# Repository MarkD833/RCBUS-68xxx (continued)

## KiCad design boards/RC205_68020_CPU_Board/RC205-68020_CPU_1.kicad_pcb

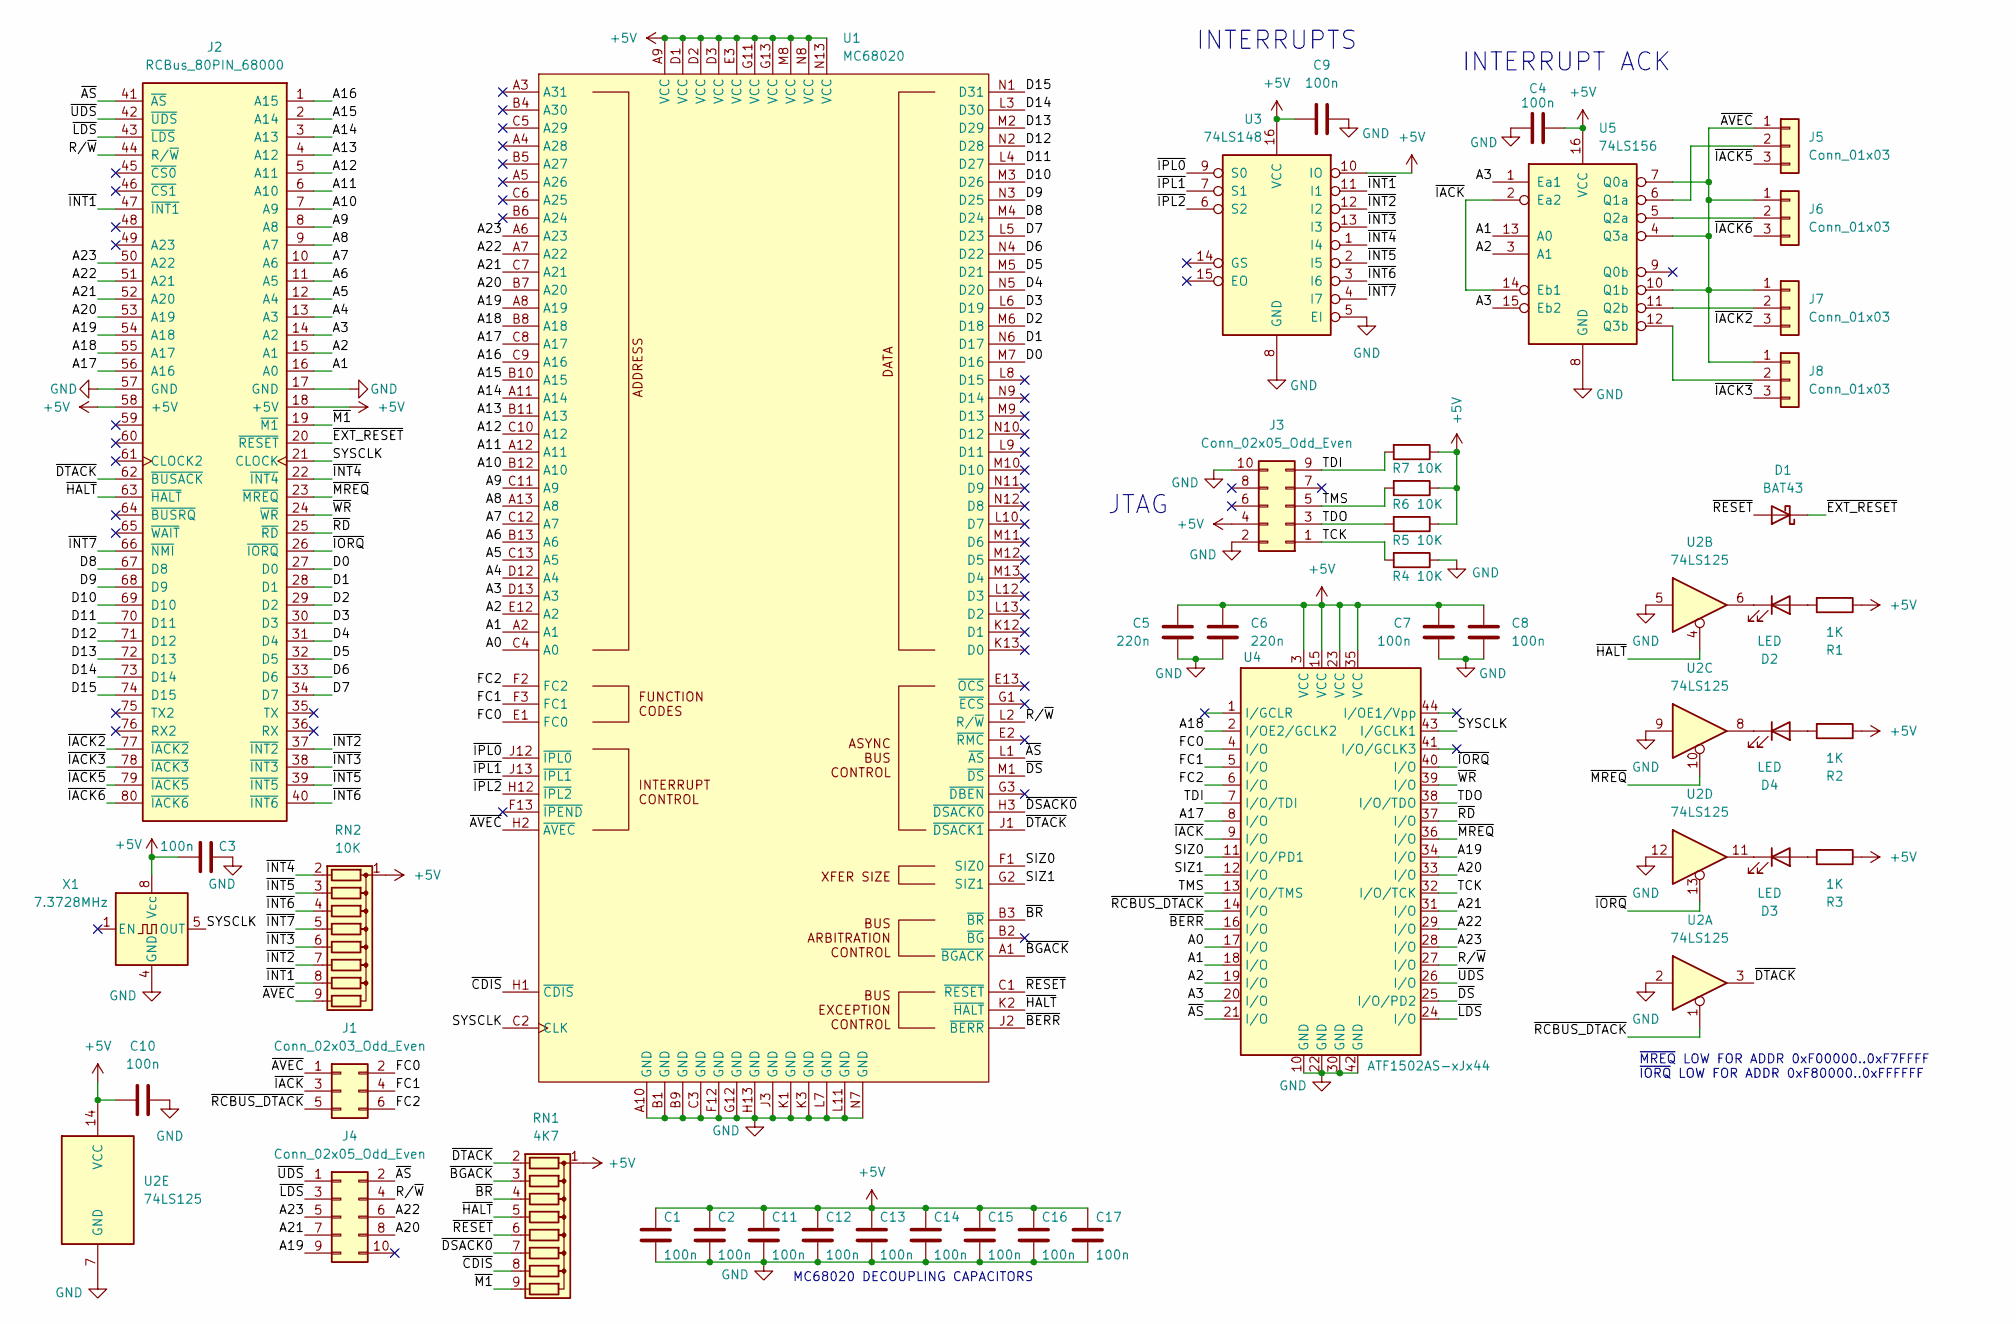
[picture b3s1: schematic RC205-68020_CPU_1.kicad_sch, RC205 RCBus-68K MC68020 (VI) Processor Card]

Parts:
C1, C2, C3, C4, C7, C8, C9, C10, C11, C12, C13, C14, C15, C16, C17: 100n; C_0805_2012Metric_Pad1.18x1.45mm_HandSolder
C5, C6: 220n; C_0805_2012Metric_Pad1.18x1.45mm_HandSolder
D1: BAT43; D_DO-35_SOD27_P7.62mm_Horizontal
D2, D3, D4: LED; LED_D3.0mm
J1: Conn_02x03_Odd_Even; PinHeader_2x03_P2.54mm_Vertical
J2: RCBus_80PIN_68000; RCBus_80p_Medium
J3, J4: Conn_02x05_Odd_Even; PinHeader_2x05_P2.54mm_Vertical
J5, J6, J7, J8: Conn_01x03; PinHeader_1x03_P2.54mm_Vertical
R1, R2, R3: 1K; R_0805_2012Metric_Pad1.20x1.40mm_HandSolder
R4, R5, R6, R7: 10K; R_0805_2012Metric_Pad1.20x1.40mm_HandSolder
RN1: 4K7; R_Array_SIP9
RN2: 10K; R_Array_SIP9
U1: MC68020; PGA114
U2: 74LS125; DIP-14_W7.62mm
U3: 74LS148; DIP-16_W7.62mm
U4: ATF1502AS-xJx44; PLCC-44_THT-Socket
U5: 74LS156; DIP-16_W7.62mm
X1: 7.3728MHz; Oscillator_DIP-8

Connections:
+5V: C1.2, C2.2, C3.2, C4.1, C5.2, C6.2, C7.1, C8.2, C9.1, C10.1, C11.2, C12.2, C13.2, C14.2, C15.2, C16.2, C17.2, J2.18 (+5V), J2.58 (+5V), J3.4, R1.1, R2.1, R3.1, R5.1, R6.1, R7.1, RN1.1 (common), RN2.1 (common), U1.A9 (VCC), U1.D1 (VCC), U1.D2 (VCC), U1.D3 (VCC), U1.E3 (VCC), U1.G11 (VCC), U1.G13 (VCC), U1.M8 (VCC), U1.N8 (VCC), U1.N13 (VCC), U2.14 (VCC), U3.10 (IO), U3.16 (VCC), U4.3 (VCC), U4.15 (VCC), U4.23 (VCC), U4.35 (VCC), U5.16 (VCC), X1.8 (Vcc)
/A0: U1.C4 (A0), U4.17 (I/O)
/A1: J2.16 (A0), U1.A2 (A1), U4.18 (I/O), U5.13 (A0)
/A2: J2.15 (A1), U1.E12 (A2), U4.19 (I/O), U5.3 (A1)
/A3: J2.14 (A2), U1.D13 (A3), U4.20 (I/O), U5.1 (Ea1), U5.15 (Eb2)
/A4: J2.13 (A3), U1.D12 (A4)
/A5: J2.12 (A4), U1.C13 (A5)
/A6: J2.11 (A5), U1.B13 (A6)
/A7: J2.10 (A6), U1.C12 (A7)
/A8: J2.9 (A7), U1.A13 (A8)
/A9: J2.8 (A8), U1.C11 (A9)
/A10: J2.7 (A9), U1.B12 (A10)
/A11: J2.6 (A10), U1.A12 (A11)
/A12: J2.5 (A11), U1.C10 (A12)
/A13: J2.4 (A12), U1.B11 (A13)
/A14: J2.3 (A13), U1.A11 (A14)
/A15: J2.2 (A14), U1.B10 (A15)
/A16: J2.1 (A15), U1.C9 (A16)
/A17: J2.56 (A16), U1.C8 (A17), U4.8 (I/O)
/A18: J2.55 (A17), U1.B8 (A18), U4.2 (I/OE2/GCLK2)
/A19: J2.54 (A18), J4.9, U1.A8 (A19), U4.34 (I/O)
/A20: J2.53 (A19), J4.8, U1.B7 (A20), U4.33 (I/O)
/A21: J2.52 (A20), J4.7, U1.C7 (A21), U4.31 (I/O)
/A22: J2.51 (A21), J4.6, U1.A7 (A22), U4.29 (I/O)
/A23: J2.50 (A22), J4.5, U1.A6 (A23), U4.28 (I/O)
/D0: J2.27 (D0), U1.M7 (D16)
/D1: J2.28 (D1), U1.N6 (D17)
/D2: J2.29 (D2), U1.M6 (D18)
/D3: J2.30 (D3), U1.L6 (D19)
/D4: J2.31 (D4), U1.N5 (D20)
/D5: J2.32 (D5), U1.M5 (D21)
/D6: J2.33 (D6), U1.N4 (D22)
/D7: J2.34 (D7), U1.L5 (D23)
/D8: J2.67 (D8), U1.M4 (D24)
/D9: J2.68 (D9), U1.N3 (D25)
/D10: J2.69 (D10), U1.M3 (D26)
/D11: J2.70 (D11), U1.L4 (D27)
/D12: J2.71 (D12), U1.N2 (D28)
/D13: J2.72 (D13), U1.M2 (D29)
/D14: J2.73 (D14), U1.L3 (D30)
/D15: J2.74 (D15), U1.N1 (D31)
/FC0: J1.2, U1.E1 (FC0), U4.4 (I/O)
/FC1: J1.4, U1.F3 (FC1), U4.5 (I/O)
/FC2: J1.6, U1.F2 (FC2), U4.6 (I/O)
/R/~W: J2.44 (R/~W), J4.4, U1.L2 (R/~W), U4.27 (I/O)
/SIZ0: U1.F1 (SIZ0), U4.11 (I/O/PD1)
/SIZ1: U1.G2 (SIZ1), U4.12 (I/O)
/SYSCLK: J2.21 (CLOCK), U1.C2 (CLK), U4.43 (I/GCLK1), X1.5 (OUT)
/TCK: J3.1, R4.2, U4.32 (I/O/TCK)
/TDI: J3.9, R7.2, U4.7 (I/O/TDI)
/TDO: J3.3, R5.2, U4.38 (I/O/TDO)
/TMS: J3.5, R6.2, U4.13 (I/O/TMS)
/~AS: J2.41 (~AS), J4.2, U1.L1 (~AS), U4.21 (I/O)
/~AVEC: J1.1, J5.1, J6.1, J7.1, J8.1, RN2.9 (R8), U1.H2 (~AVEC), U5.4 (Q3a), U5.7 (Q0a), U5.10 (Q1b)
/~BERR: U1.J2 (~BERR), U4.16 (I/O)
/~BGACK: RN1.3 (R2), U1.A1 (~BGACK)
/~BR: RN1.4 (R3), U1.B3 (~BR)
/~CDIS: RN1.8 (R7), U1.H1 (~CDIS)
/~DSACK0: RN1.7 (R6), U1.H3 (~DSACK0)
/~DS: U1.M1 (~DS), U4.25 (I/O/PD2)
/~DTACK: J2.62 (~BUSACK), RN1.2 (R1), U1.J1 (~DSACK1), U2.3
/~EXT_RESET: D1.1 (K), J2.20 (~RESET)
/~HALT: J2.63 (~HALT), RN1.5 (R4), U1.K2 (~HALT), U2.4
/~IACK2: J2.77 (~IACK2), J7.3
/~IACK3: J2.78 (~IACK3), J8.3
/~IACK5: J2.79 (~IACK5), J5.3
/~IACK6: J2.80 (~IACK6), J6.3
/~IACK: J1.3, U4.9 (I/O), U5.2 (Ea2), U5.14 (Eb1)
/~INT1: J2.47 (~INT1), RN2.8 (R7), U3.11 (I1)
/~INT2: J2.37 (~INT2), RN2.7 (R6), U3.12 (I2)
/~INT3: J2.38 (~INT3), RN2.6 (R5), U3.13 (I3)
/~INT4: J2.22 (~INT4), RN2.2 (R1), U3.1 (I4)
/~INT5: J2.39 (~INT5), RN2.3 (R2), U3.2 (I5)
/~INT6: J2.40 (~INT6), RN2.4 (R3), U3.3 (I6)
/~INT7: J2.66 (~NMI), RN2.5 (R4), U3.4 (I7)
/~IORQ: J2.26 (~IORQ), U2.13, U4.40 (I/O)
/~IPL0: U1.J12 (~IPL0), U3.9 (S0)
/~IPL1: U1.J13 (~IPL1), U3.7 (S1)
/~IPL2: U1.H12 (~IPL2), U3.6 (S2)
/~LDS: J2.43 (~LDS), J4.3, U4.24 (I/O)
/~M1: J2.19 (~M1), RN1.9 (R8)
/~MREQ: J2.23 (~MREQ), U2.10, U4.36 (I/O)
/~RCBUS_DTACK: J1.5, U2.1, U4.14 (I/O)
/~RD: J2.25 (~RD), U4.37 (I/O)
/~RESET: D1.2 (A), RN1.6 (R5), U1.C1 (~RESET)
/~UDS: J2.42 (~UDS), J4.1, U4.26 (I/O)
/~WR: J2.24 (~WR), U4.39 (I/O)
GND: C1.1, C2.1, C3.1, C4.2, C5.1, C6.1, C7.2, C8.1, C9.2, C10.2, C11.1, C12.1, C13.1, C14.1, C15.1, C16.1, C17.1, J2.17 (GND), J2.57 (GND), J3.2, J3.10, R4.1, U1.A10 (GND), U1.B1 (GND), U1.B9 (GND), U1.C3 (GND), U1.F12 (GND), U1.G12 (GND), U1.H13 (GND), U1.J3 (GND), U1.K1 (GND), U1.K3 (GND), U1.L7 (GND), U1.L11 (GND), U1.N7 (GND), U2.2, U2.5, U2.7 (GND), U2.9, U2.12, U3.5 (EI), U3.8 (GND), U4.10 (GND), U4.22 (GND), U4.30 (GND), U4.42 (GND), U5.8 (GND), X1.4 (GND)
unnamed: D2.2 (A), R1.2
unnamed: D2.1 (K), U2.6
unnamed: D3.2 (A), R3.2
unnamed: D3.1 (K), U2.11
unnamed: D4.2 (A), R2.2
unnamed: D4.1 (K), U2.8
unnamed: J5.2, U5.6 (Q1a)
unnamed: J6.2, U5.5 (Q2a)
unnamed: J7.2, U5.11 (Q2b)
unnamed: J8.2, U5.12 (Q3b)

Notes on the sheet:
MC68020 DECOUPLING CAPACITORS
INTERRUPTS
~{MREQ} LOW FOR ADDR 0xF00000..0xF7FFFF ~{IORQ} LOW FOR ADDR 0xF80000..0xFFFFFF
INTERRUPT ACK
JTAG

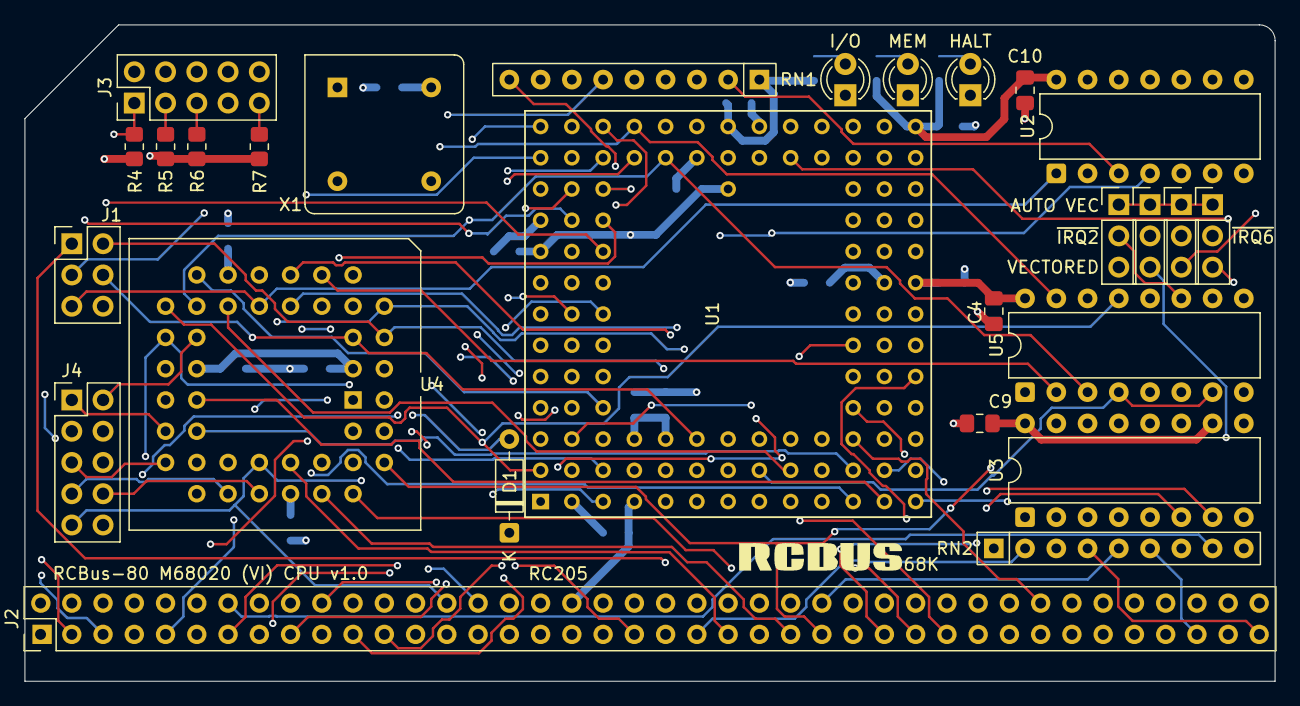
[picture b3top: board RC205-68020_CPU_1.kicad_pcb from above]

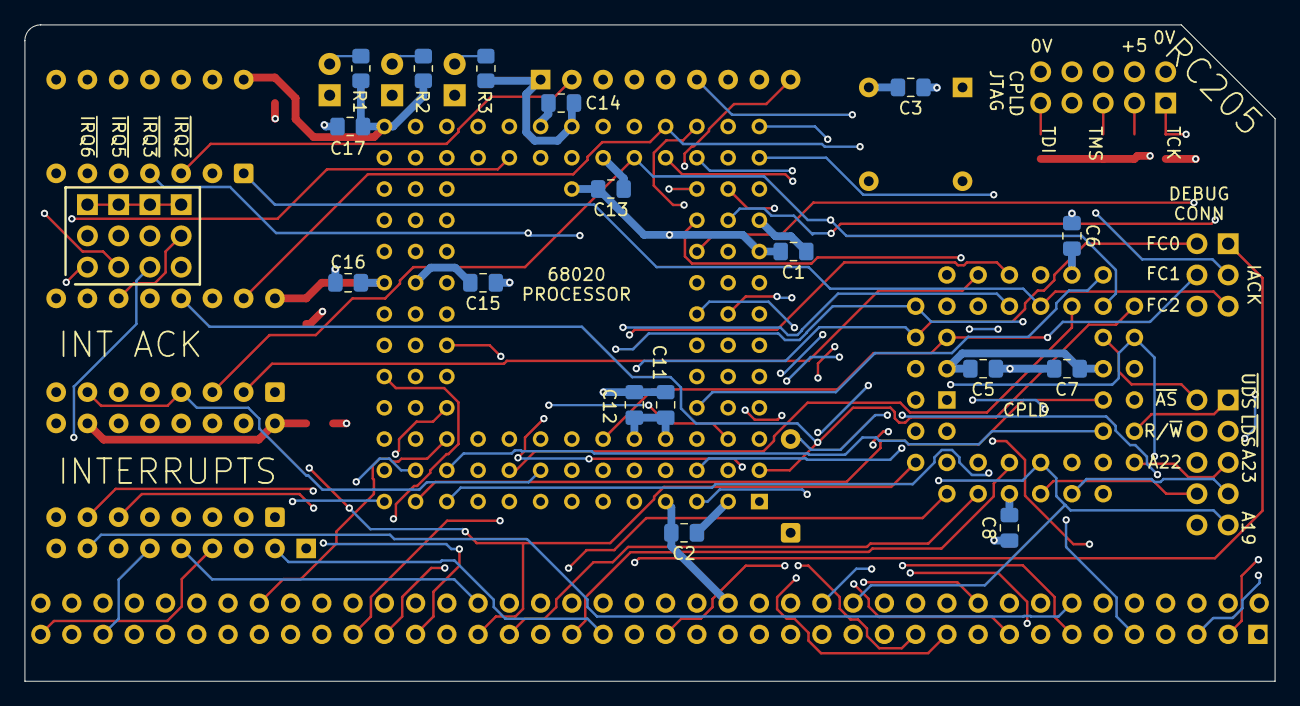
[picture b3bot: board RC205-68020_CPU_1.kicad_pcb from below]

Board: 4 copper layers, 101.6 x 53.3 mm, 44 parts (17 on the bottom side), 98 nets.

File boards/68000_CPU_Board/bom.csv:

Designator,Footprint,Quantity,Value,LCSC Part #
"C1, C10, C11, C2, C3, C5, C6, C7, C8, C9",C_Disc_D5.0mm_W2.5mm_P2.50mm,10,100n,
"D1, D2",D_DO-35_SOD27_P7.62mm_Horizontal,2,BAT43,
"D3, D4, D5",LED_D3.0mm,3,LED,
J1,PinHeader_2x04_P2.54mm_Vertical,1,Conn_02x04_Odd_Even,
J2,RCBus_80p_Medium,1,RCBus_80PIN_68000,
J4,PinHeader_1x02_P2.54mm_Vertical,1,Conn_01x02,
"R1, R2, R3",R_Axial_DIN0207_L6.3mm_D2.5mm_P7.62mm_Horizontal,3,1K,
RN1,R_Array_SIP9,1,4K7,
RN2,R_Array_SIP9,1,10K,
U1,PLCC-68_THT-Socket,1,MC68000FN,
U2,DIP-14_W7.62mm_Socket,1,74LS125,
U3,DIP-16_W7.62mm_Socket,1,74LS148,
U4,DIP-14_W7.62mm_Socket,1,74LS10,
U5,DIP-16_W7.62mm_Socket,1,74LS139,
"U6, U8",DIP-16_W7.62mm_Socket,2,74LS175,
U9,DIP-14_W7.62mm_Socket,1,74LS00,
X1,Oscillator_DIP-8,1,CXO_DIP8,

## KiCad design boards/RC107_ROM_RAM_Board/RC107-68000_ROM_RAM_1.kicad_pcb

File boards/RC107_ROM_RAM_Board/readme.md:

# ROM & RAM board - V2 - 1M ROM + 1M RAM

# Details
The ROM & RAM board is designed to plug into an RCBus-80 backplane with support for 1M ROM (via 2x SST39SF040 FLASH chips) and 1M RAM (via 2x Alliance Memory AS6C4008 SRAMs). The FLASH chips and SRAMs are used as a pair to allow 16-bit wide memory accesses.

## Address Decoding
The address decoding is carried out by a 74LS138 and divides the lower 8Mb of memory space into eight 1Mb blocks. Each pair of chips can be assigned to any of the 8 chip selects - but not both pairs to the same chip select.

**Note:** If this is the only memory board in the 68000 system, then a pair of FLASH chips should be assigned to /CS0 so that the 68000 finds the stack pointer and program counter on boot.

**Note:** If this board is used with an MC68302 processor, then see the note further down regarding the ability to remap the ROM & RAM devices.

## Bus Width 
A 74LS139 generates the read and write signals for each of the memory chips and takes care of byte or word accesses.

## DTACK
A 74LS125 is used to generate a simple /DTACK signal driven directly from the EEPROM and SRAM chip select signals without any wait period.

# Board Assembly
Assembly of the board should be fairly straightforward as there are no surface mount devices to deal with.

Note the location of the decoupling capacitors for the memory devices are located within the IC sockets. THese decoupling capacitors should be bent over so that they do not interfere with the insertion of the memory chips.
 
When fitting the 80-pin right angle connector, initially only solder a couple of pins at opposite ends of the connector so that you can make any adjustments if the board is not vertical when fitted to the backplane.

Do not mix ROM & RAM chips in the same bank.

# Memory Bank Configuration
The pinout of the 32-pin FLASH and SRAM chips are slightly different and in order to accommodate both types, a pair of jumpers need to be set per chip. J6,J7,J8 & J9 set the memory type fitted to memory bank #0 and J2,J3,J4 & J5 set the memory type fitted to memory bank #1.

# Jumpers
+ FLASH ROM chips installed in Bank #1
  + J2: Jumper pins 1-2
  + J3: Jumper pins 2-3
  + J4: Jumper pins 1-2
  + J5: Jumper pins 2-3
+ RAM chips installed in Bank #1
  + J2: Jumper pins 2-3
  + J3: Jumper pins 1-2
  + J4: Jumper pins 2-3
  + J5: Jumper pins 1-2
+ FLASH ROM chips installed in Bank #0
  + J6: Jumper pins 2-3
  + J7: Jumper pins 1-2
  + J8: Jumper pins 2-3
  + J9: Jumper pins 1-2
+ RAM chips installed in Bank #0
  + J6: Jumper pins 1-2
  + J7: Jumper pins 2-3
  + J8: Jumper pins 1-2
  + J9: Jumper pins 2-3
+ J10: Memory Address selection
  + $000000 .. $0FFFFF
  + $100000 .. $1FFFFF
  + $200000 .. $2FFFFF
  + $300000 .. $3FFFFF
  + $400000 .. $4FFFFF
  + $500000 .. $5FFFFF
+ J11 (with J10): Specify the memory address for bank #0
+ J12 (with J10): Specify the memory address for bank #1
+ JP1: Solder link to connect RCBus /CS_ROM to /CS_BANK0 (Bank 0 must have FLASH memory fitted).
+ JP2: Solder link to connect RCBus /CS_RAM to /CS_BANK1 (Bank 1 must have SRAM memory fitted).

# MC68302 ROM & RAM Remapping

If the version of the MC68302 monitor is used that makes use of remapping the chip select signals, then the following hardware changes are required to this board:
  + U1 (74LS125) should be removed as the 68302 is configured to generate the /DTACK signals for /CS0 and /CS1 itself
  + U5 (74LS138) should be removed as the 68302 is configured to generate the chip select signals itself
  + Solder links JP1 and JP2 on the rear of the board must be made.
  
# Errors
Nothing yet - but give it time :-(

# History
+ v2.0 - corrected missing /CS signals, fixed J4 & J5 pitch, added 10K pullups to /CS lines
+ v1.0 - initial designed

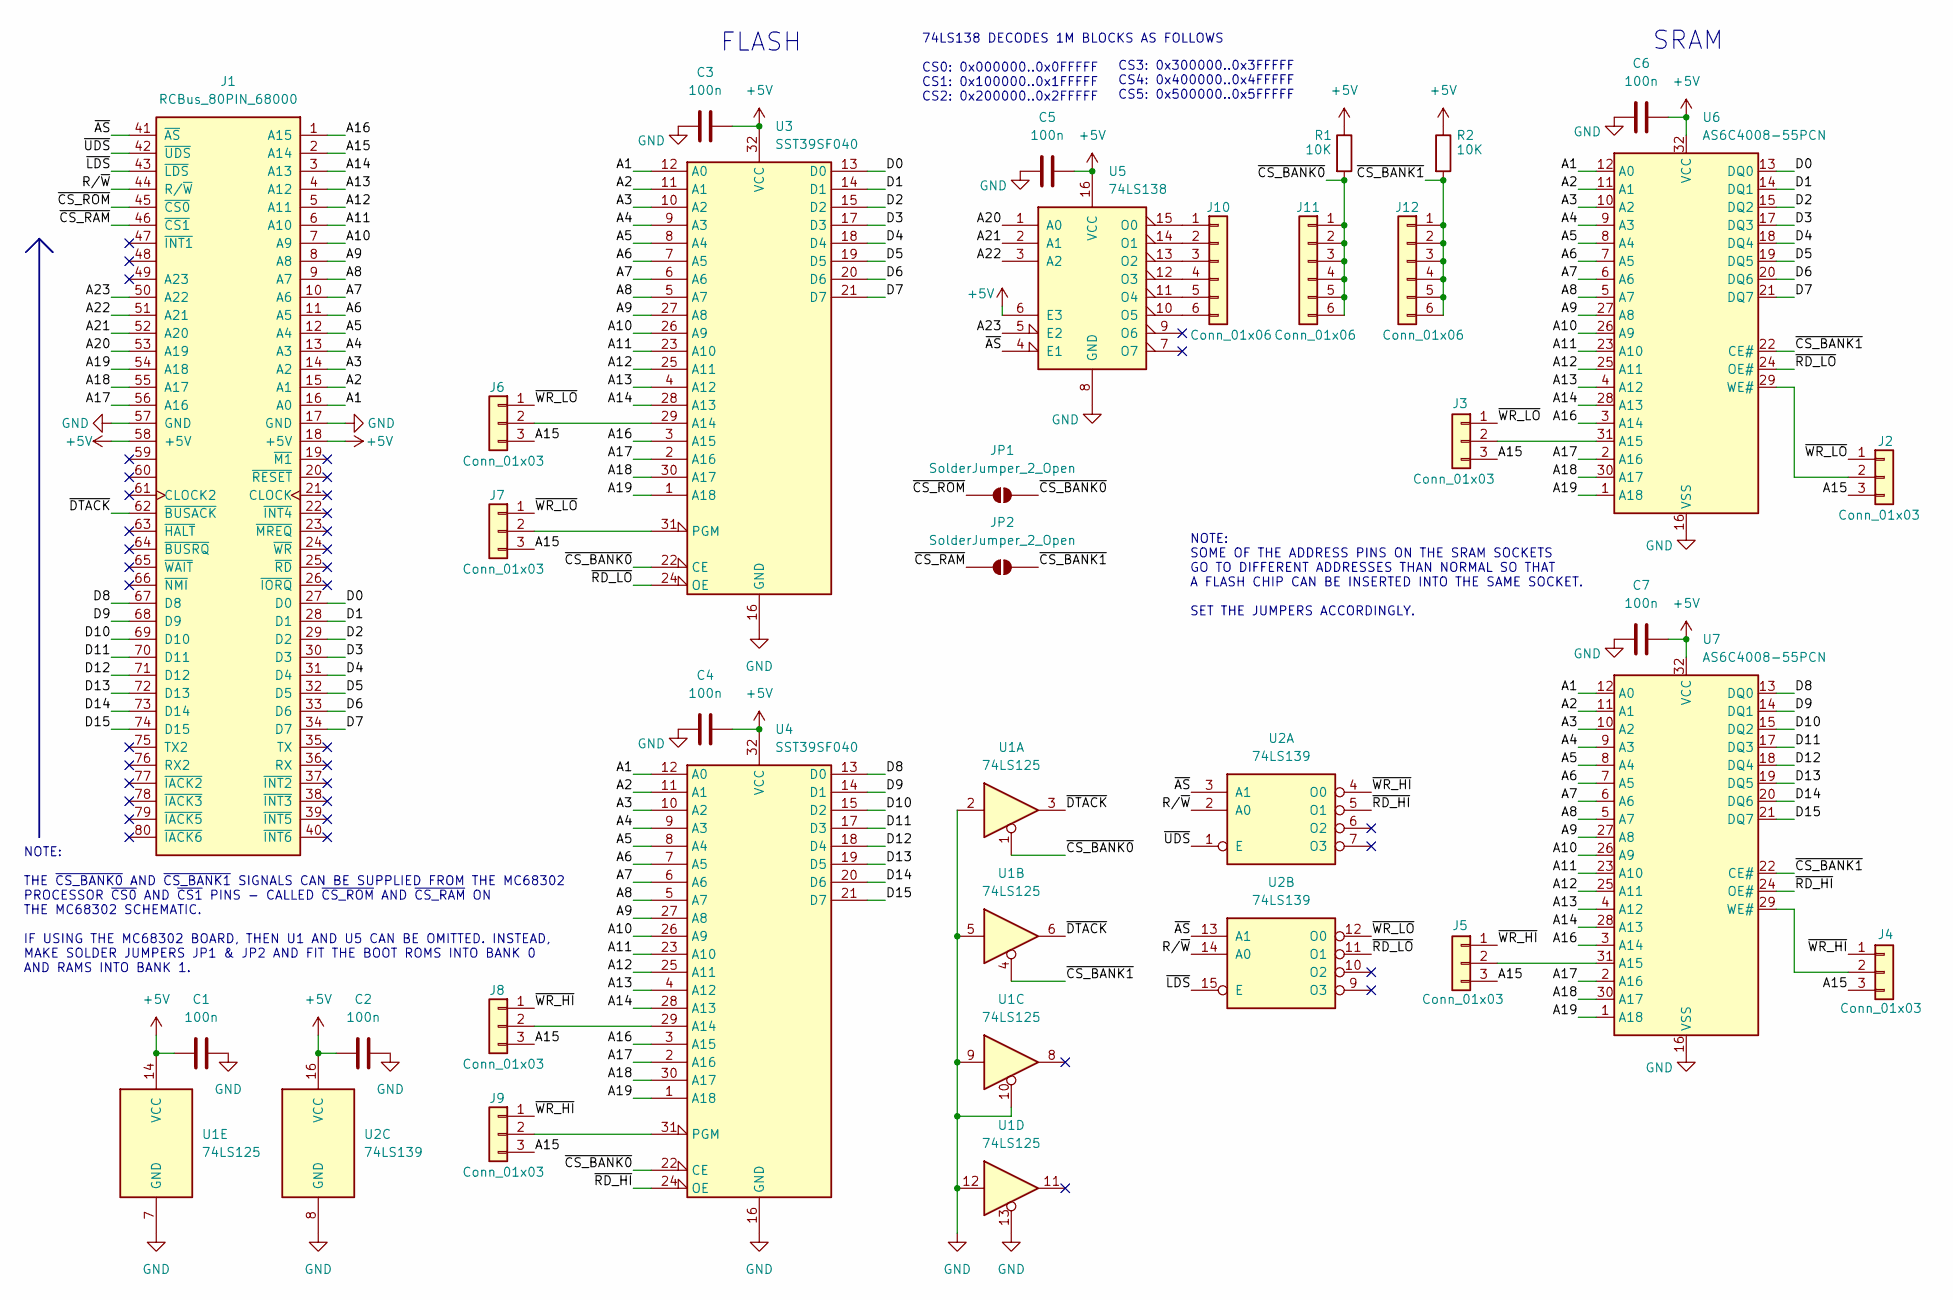
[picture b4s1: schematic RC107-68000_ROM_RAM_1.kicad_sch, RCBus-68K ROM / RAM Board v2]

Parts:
C1, C2, C3, C4, C5, C6, C7: 100n; C_Disc_D5.0mm_W2.5mm_P2.50mm
J1: RCBus_80PIN_68000; RCBus_80p_Medium
J2, J3, J4, J5, J6, J7, J8, J9: Conn_01x03; PinHeader_1x03_P2.54mm_Vertical
J10, J11, J12: Conn_01x06; PinHeader_1x06_P2.54mm_Vertical
JP1, JP2: SolderJumper_2_Open; SolderJumper-2_P1.3mm_Open_Pad1.0x1.5mm
R1, R2: 10K; R_Axial_DIN0207_L6.3mm_D2.5mm_P7.62mm_Horizontal
U1: 74LS125; DIP-14_W7.62mm
U2: 74LS139; DIP-16_W7.62mm
U3, U4: SST39SF040; DIP-32_W15.24mm
U5: 74LS138; DIP-16_W7.62mm
U6, U7: AS6C4008-55PCN; DIP-32_W15.24mm

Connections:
+5V: C1.1, C2.1, C3.2, C4.2, C5.2, C6.2, C7.2, J1.18 (+5V), J1.58 (+5V), R1.1, R2.1, U1.14 (VCC), U2.16 (VCC), U3.32 (VCC), U4.32 (VCC), U5.6 (E3), U5.16 (VCC), U6.32 (VCC), U7.32 (VCC)
/A1: J1.16 (A0), U3.12 (A0), U4.12 (A0), U6.12 (A0), U7.12 (A0)
/A2: J1.15 (A1), U3.11 (A1), U4.11 (A1), U6.11 (A1), U7.11 (A1)
/A3: J1.14 (A2), U3.10 (A2), U4.10 (A2), U6.10 (A2), U7.10 (A2)
/A4: J1.13 (A3), U3.9 (A3), U4.9 (A3), U6.9 (A3), U7.9 (A3)
/A5: J1.12 (A4), U3.8 (A4), U4.8 (A4), U6.8 (A4), U7.8 (A4)
/A6: J1.11 (A5), U3.7 (A5), U4.7 (A5), U6.7 (A5), U7.7 (A5)
/A7: J1.10 (A6), U3.6 (A6), U4.6 (A6), U6.6 (A6), U7.6 (A6)
/A8: J1.9 (A7), U3.5 (A7), U4.5 (A7), U6.5 (A7), U7.5 (A7)
/A9: J1.8 (A8), U3.27 (A8), U4.27 (A8), U6.27 (A8), U7.27 (A8)
/A10: J1.7 (A9), U3.26 (A9), U4.26 (A9), U6.26 (A9), U7.26 (A9)
/A11: J1.6 (A10), U3.23 (A10), U4.23 (A10), U6.23 (A10), U7.23 (A10)
/A12: J1.5 (A11), U3.25 (A11), U4.25 (A11), U6.25 (A11), U7.25 (A11)
/A13: J1.4 (A12), U3.4 (A12), U4.4 (A12), U6.4 (A12), U7.4 (A12)
/A14: J1.3 (A13), U3.28 (A13), U4.28 (A13), U6.28 (A13), U7.28 (A13)
/A15: J1.2 (A14), J2.3, J3.3, J4.3, J5.3, J6.3, J7.3, J8.3, J9.3
/A16: J1.1 (A15), U3.3 (A15), U4.3 (A15), U6.3 (A14), U7.3 (A14)
/A17: J1.56 (A16), U3.2 (A16), U4.2 (A16), U6.2 (A16), U7.2 (A16)
/A18: J1.55 (A17), U3.30 (A17), U4.30 (A17), U6.30 (A17), U7.30 (A17)
/A19: J1.54 (A18), U3.1 (A18), U4.1 (A18), U6.1 (A18), U7.1 (A18)
/A20: J1.53 (A19), U5.1 (A0)
/A21: J1.52 (A20), U5.2 (A1)
/A22: J1.51 (A21), U5.3 (A2)
/A23: J1.50 (A22), U5.5 (E2)
/D0: J1.27 (D0), U3.13 (D0), U6.13 (DQ0)
/D1: J1.28 (D1), U3.14 (D1), U6.14 (DQ1)
/D2: J1.29 (D2), U3.15 (D2), U6.15 (DQ2)
/D3: J1.30 (D3), U3.17 (D3), U6.17 (DQ3)
/D4: J1.31 (D4), U3.18 (D4), U6.18 (DQ4)
/D5: J1.32 (D5), U3.19 (D5), U6.19 (DQ5)
/D6: J1.33 (D6), U3.20 (D6), U6.20 (DQ6)
/D7: J1.34 (D7), U3.21 (D7), U6.21 (DQ7)
/D8: J1.67 (D8), U4.13 (D0), U7.13 (DQ0)
/D9: J1.68 (D9), U4.14 (D1), U7.14 (DQ1)
/D10: J1.69 (D10), U4.15 (D2), U7.15 (DQ2)
/D11: J1.70 (D11), U4.17 (D3), U7.17 (DQ3)
/D12: J1.71 (D12), U4.18 (D4), U7.18 (DQ4)
/D13: J1.72 (D13), U4.19 (D5), U7.19 (DQ5)
/D14: J1.73 (D14), U4.20 (D6), U7.20 (DQ6)
/D15: J1.74 (D15), U4.21 (D7), U7.21 (DQ7)
/R/~W: J1.44 (R/~W), U2.2 (A0), U2.14 (A0)
/~AS: J1.41 (~AS), U2.3 (A1), U2.13 (A1), U5.4 (E1)
/~CS_BANK0: J11.1, J11.2, J11.3, J11.4, J11.5, J11.6, JP1.2 (B), R1.2, U1.1, U3.22 (CE), U4.22 (CE)
/~CS_BANK1: J12.1, J12.2, J12.3, J12.4, J12.5, J12.6, JP2.2 (B), R2.2, U1.4, U6.22 (CE#), U7.22 (CE#)
/~CS_RAM: J1.46 (~CS1), JP2.1 (A)
/~CS_ROM: J1.45 (~CS0), JP1.1 (A)
/~DTACK: J1.62 (~BUSACK), U1.3, U1.6
/~LDS: J1.43 (~LDS), U2.15 (E)
/~RD_HI: U2.5 (O1), U4.24 (OE), U7.24 (OE#)
/~RD_LO: U2.11 (O1), U3.24 (OE), U6.24 (OE#)
/~UDS: J1.42 (~UDS), U2.1 (E)
/~WR_HI: J4.1, J5.1, J8.1, J9.1, U2.4 (O0)
/~WR_LO: J2.1, J3.1, J6.1, J7.1, U2.12 (O0)
GND: C1.2, C2.2, C3.1, C4.1, C5.1, C6.1, C7.1, J1.17 (GND), J1.57 (GND), U1.2, U1.5, U1.7 (GND), U1.9, U1.10, U1.12, U1.13, U2.8 (GND), U3.16 (GND), U4.16 (GND), U5.8 (GND), U6.16 (VSS), U7.16 (VSS)
unnamed: J2.2, U6.29 (WE#)
unnamed: J3.2, U6.31 (A15)
unnamed: J4.2, U7.29 (WE#)
unnamed: J5.2, U7.31 (A15)
unnamed: J6.2, U3.29 (A14)
unnamed: J7.2, U3.31 (PGM)
unnamed: J8.2, U4.29 (A14)
unnamed: J9.2, U4.31 (PGM)
unnamed: J10.1, U5.15 (O0)
unnamed: J10.2, U5.14 (O1)
unnamed: J10.3, U5.13 (O2)
unnamed: J10.4, U5.12 (O3)
unnamed: J10.5, U5.11 (O4)
unnamed: J10.6, U5.10 (O5)

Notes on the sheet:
CS3: 0x300000..0x3FFFFF CS4: 0x400000..0x4FFFFF CS5: 0x500000..0x5FFFFF
FLASH
NOTE: THE ~{CS_BANK0} AND ~{CS_BANK1} SIGNALS CAN BE SUPPLIED FROM THE MC68302 PROCESSOR ~{CS0} AND ~{CS1} PINS - CALLED ~{CS_ROM} AND ~{CS_RAM} ON THE MC68302 SCHEMATIC. IF USING THE MC68302 BOARD, THEN U1 AND U5 CAN BE OMITTED. INSTEAD, MAKE SOLDER JUMPERS JP1 & JP2 AND FIT THE BOOT ROMS INTO BAN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
74LS138 DECODES 1M BLOCKS AS FOLLOWS CS0: 0x000000..0x0FFFFF CS1: 0x100000..0x1FFFFF CS2: 0x200000..0x2FFFFF
NOTE: SOME OF THE ADDRESS PINS ON THE SRAM SOCKETS GO TO DIFFERENT ADDRESSES THAN NORMAL SO THAT A FLASH CHIP CAN BE INSERTED INTO THE SAME SOCKET. SET THE JUMPERS ACCORDINGLY.
SRAM

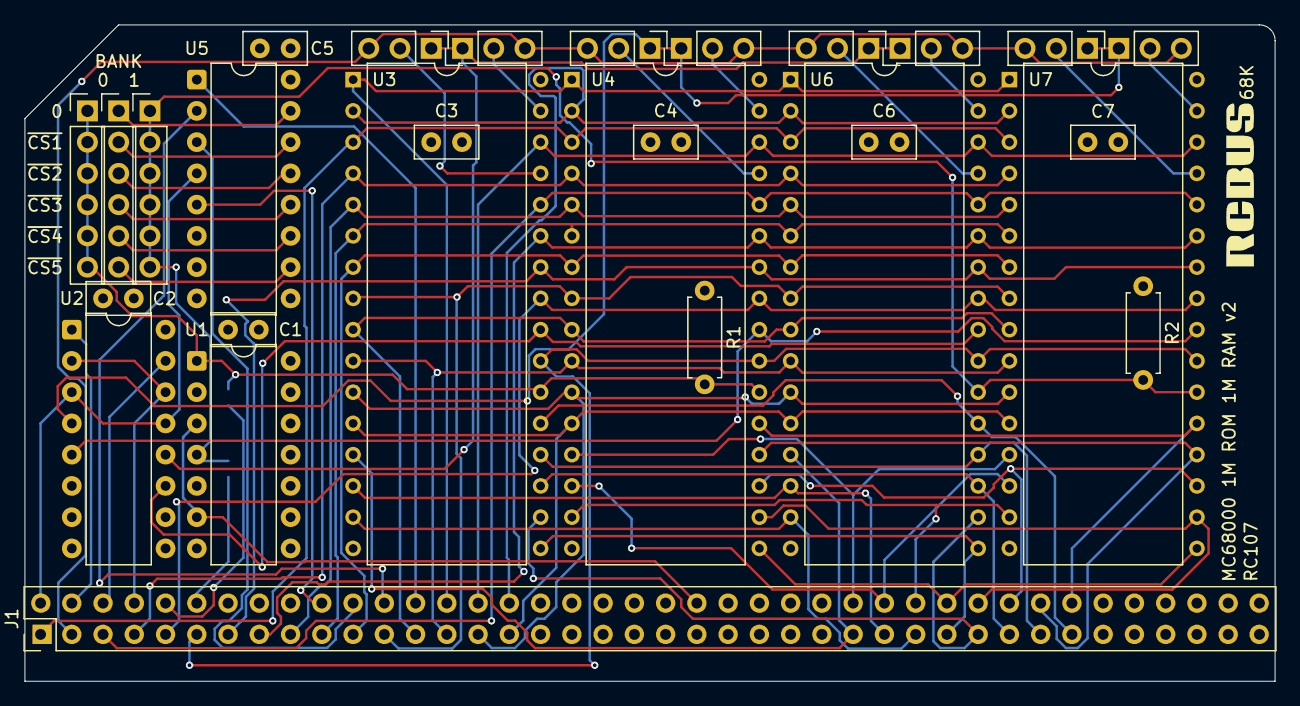
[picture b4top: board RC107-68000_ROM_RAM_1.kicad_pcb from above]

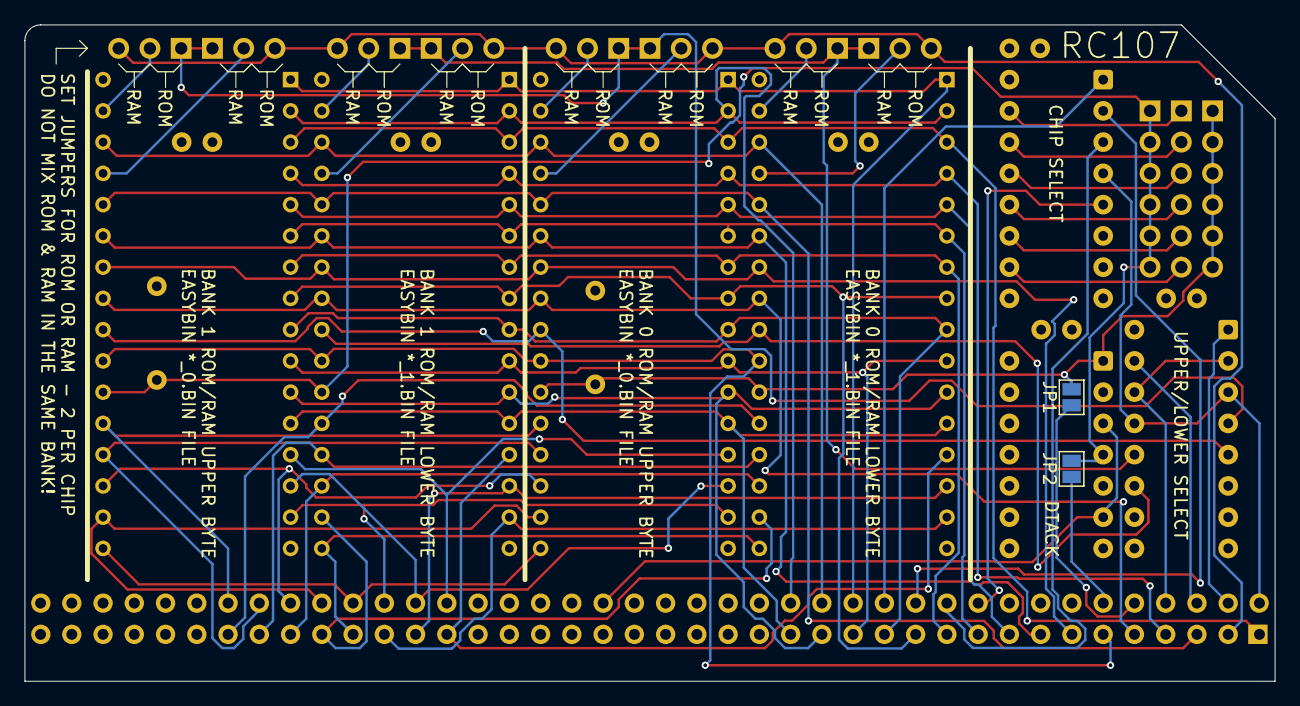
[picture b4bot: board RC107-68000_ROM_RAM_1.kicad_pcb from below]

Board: 4 copper layers, 101.6 x 53.3 mm, 30 parts (2 on the bottom side), 68 nets.

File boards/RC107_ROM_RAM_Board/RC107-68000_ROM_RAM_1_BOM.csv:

"Reference","Value","Qty","Description"
"C1,C2,C3,C4,C5,C6,C7","100n","7","Unpolarized ceramic capacitor"
"J1","RCBus_80PIN_68000","1","Generic connector, double row, 02x40, right angle"
"J2,J3,J4,J5,J6,J7,J8,J9","Conn_01x03","8","Generic connector, single row, 01x03"
"J10,J11,J12","Conn_01x06","3","Generic connector, single row, 01x06"
"R1,R2","10K","2","Resistor"
"U1","74LS125","1","Quad buffer 3-State outputs"
"U2","74LS139","1","Dual Decoder 1 of 4, Active low outputs"
"U3,U4","SST39SF040","2","Silicon Storage Technology (SSF) 512k x 8 Flash ROM"
"U5","74LS138","1","Decoder 3 to 8 active low outputs"
"U6,U7","AS6C4008-55PCN","2","512K x 8 Low Power CMOS RAM, DIP-32"

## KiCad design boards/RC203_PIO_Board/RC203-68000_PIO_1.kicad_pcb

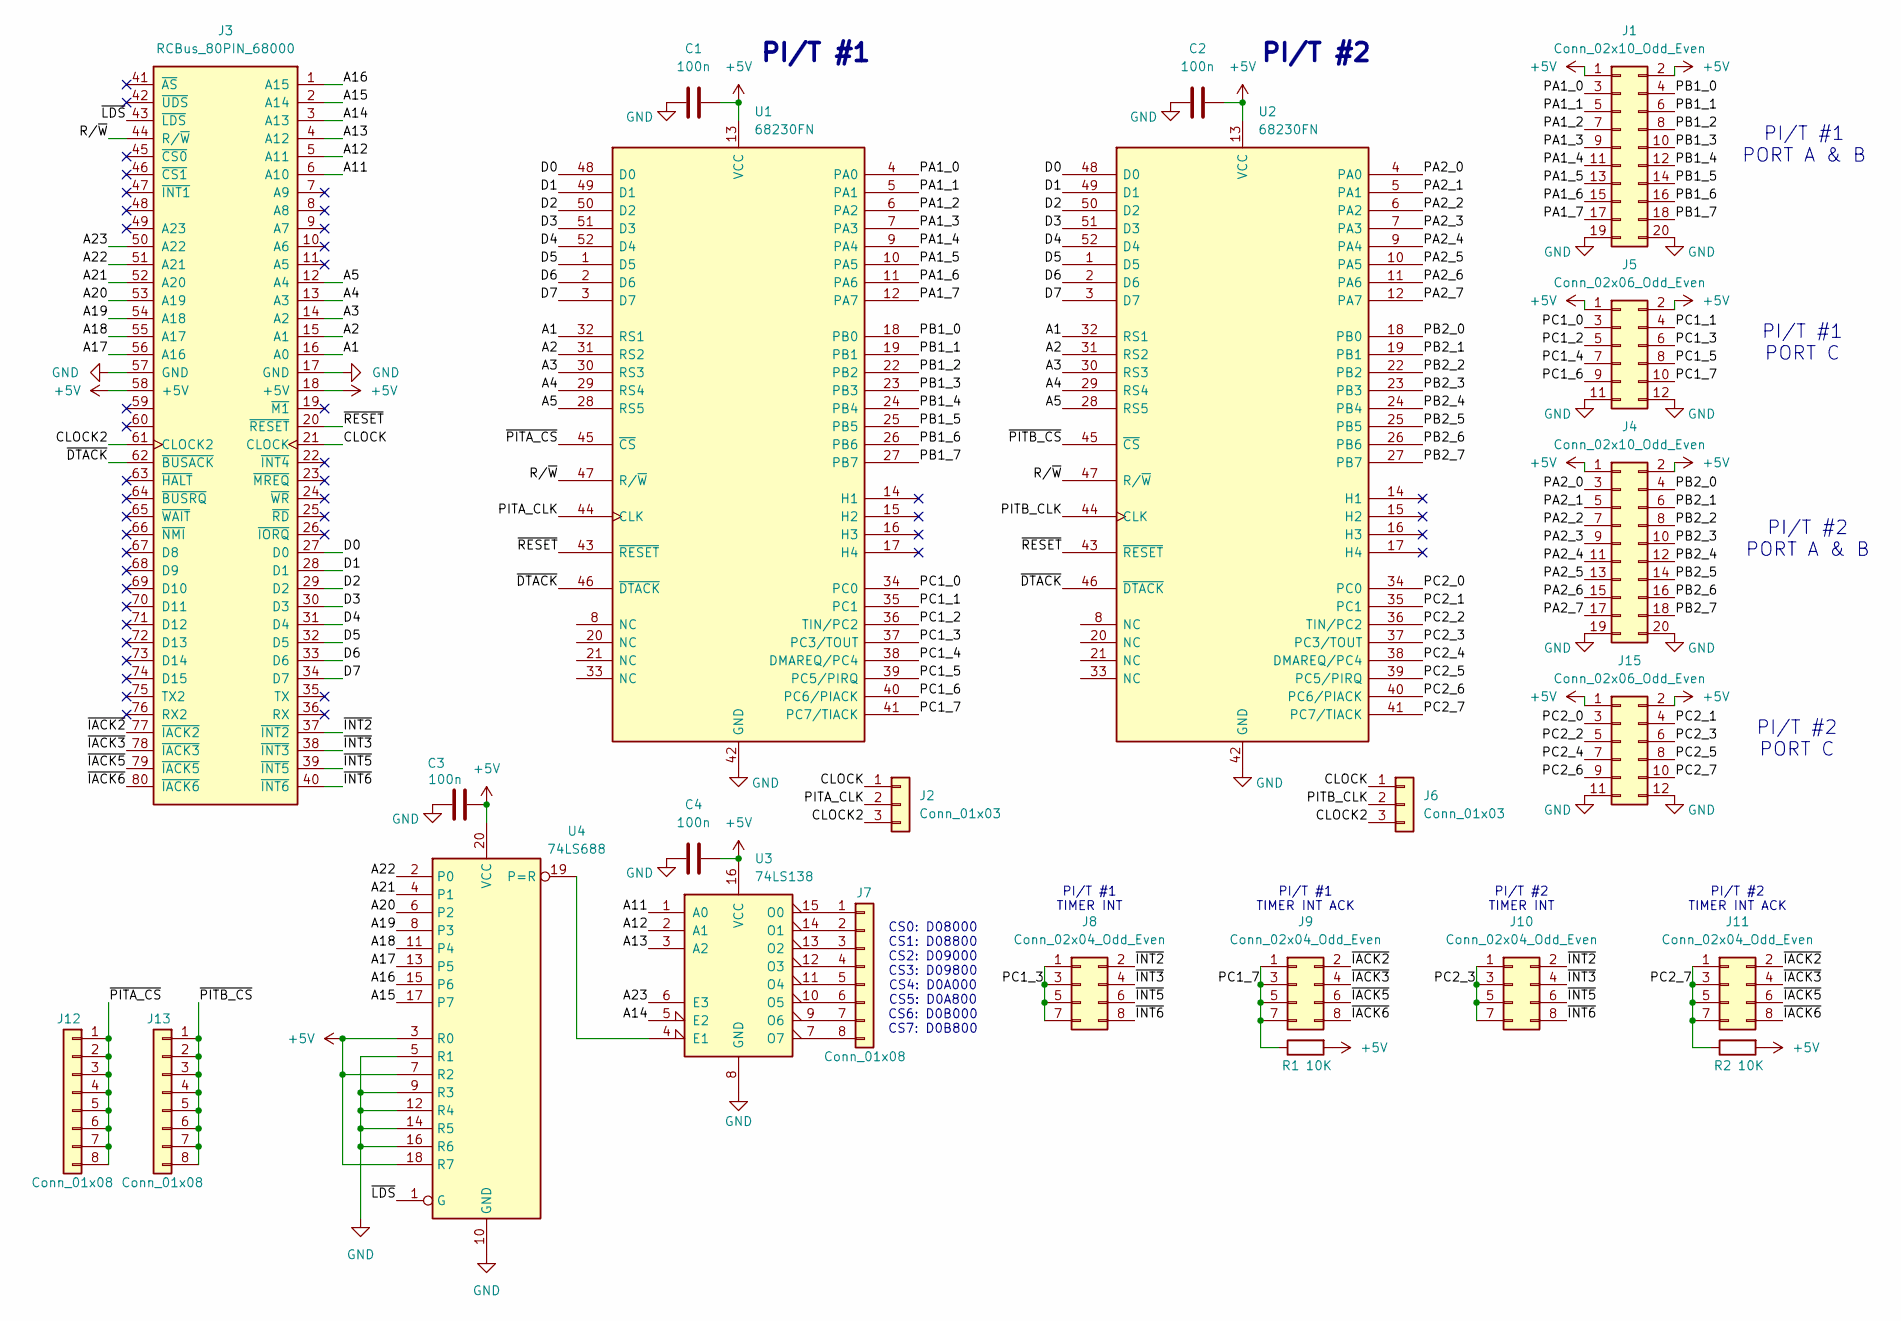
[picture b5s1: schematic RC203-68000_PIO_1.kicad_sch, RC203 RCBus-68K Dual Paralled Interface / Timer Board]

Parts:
C1, C2, C3, C4: 100n; C_Disc_D5.0mm_W2.5mm_P2.50mm
J1, J4: Conn_02x10_Odd_Even; PinHeader_2x10_P2.54mm_Horizontal
J2, J6: Conn_01x03; PinHeader_1x03_P2.54mm_Vertical
J3: RCBus_80PIN_68000; RCBus_80p_Medium
J5, J15: Conn_02x06_Odd_Even; PinHeader_2x06_P2.54mm_Horizontal
J7, J12, J13: Conn_01x08; PinHeader_1x08_P2.54mm_Vertical
J8, J9, J10, J11: Conn_02x04_Odd_Even; PinHeader_2x04_P2.54mm_Vertical
R1, R2: 10K; R_Axial_DIN0207_L6.3mm_D2.5mm_P7.62mm_Horizontal
U1, U2: 68230FN; PLCC-52_THT-Socket
U3: 74LS138; DIP-16_W7.62mm
U4: 74LS688; DIP-20_W7.62mm

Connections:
+5V: C1.1, C2.1, C3.2, C4.2, J1.1, J1.2, J3.18 (+5V), J3.58 (+5V), J4.1, J4.2, J5.1, J5.2, J15.1, J15.2, R1.2, R2.2, U1.13 (VCC), U2.13 (VCC), U3.16 (VCC), U4.3 (R0), U4.7 (R2), U4.18 (R7), U4.20 (VCC)
/A1: J3.16 (A0), U1.32 (RS1), U2.32 (RS1)
/A2: J3.15 (A1), U1.31 (RS2), U2.31 (RS2)
/A3: J3.14 (A2), U1.30 (RS3), U2.30 (RS3)
/A4: J3.13 (A3), U1.29 (RS4), U2.29 (RS4)
/A5: J3.12 (A4), U1.28 (RS5), U2.28 (RS5)
/A11: J3.6 (A10), U3.1 (A0)
/A12: J3.5 (A11), U3.2 (A1)
/A13: J3.4 (A12), U3.3 (A2)
/A14: J3.3 (A13), U3.5 (E2)
/A15: J3.2 (A14), U4.17 (P7)
/A16: J3.1 (A15), U4.15 (P6)
/A17: J3.56 (A16), U4.13 (P5)
/A18: J3.55 (A17), U4.11 (P4)
/A19: J3.54 (A18), U4.8 (P3)
/A20: J3.53 (A19), U4.6 (P2)
/A21: J3.52 (A20), U4.4 (P1)
/A22: J3.51 (A21), U4.2 (P0)
/A23: J3.50 (A22), U3.6 (E3)
/CLOCK: J2.1, J3.21 (CLOCK), J6.1
/CLOCK2: J2.3, J3.61 (CLOCK2), J6.3
/D0: J3.27 (D0), U1.48 (D0), U2.48 (D0)
/D1: J3.28 (D1), U1.49 (D1), U2.49 (D1)
/D2: J3.29 (D2), U1.50 (D2), U2.50 (D2)
/D3: J3.30 (D3), U1.51 (D3), U2.51 (D3)
/D4: J3.31 (D4), U1.52 (D4), U2.52 (D4)
/D5: J3.32 (D5), U1.1 (D5), U2.1 (D5)
/D6: J3.33 (D6), U1.2 (D6), U2.2 (D6)
/D7: J3.34 (D7), U1.3 (D7), U2.3 (D7)
/PA1_0: J1.3, U1.4 (PA0)
/PA1_1: J1.5, U1.5 (PA1)
/PA1_2: J1.7, U1.6 (PA2)
/PA1_3: J1.9, U1.7 (PA3)
/PA1_4: J1.11, U1.9 (PA4)
/PA1_5: J1.13, U1.10 (PA5)
/PA1_6: J1.15, U1.11 (PA6)
/PA1_7: J1.17, U1.12 (PA7)
/PA2_0: J4.3, U2.4 (PA0)
/PA2_1: J4.5, U2.5 (PA1)
/PA2_2: J4.7, U2.6 (PA2)
/PA2_3: J4.9, U2.7 (PA3)
/PA2_4: J4.11, U2.9 (PA4)
/PA2_5: J4.13, U2.10 (PA5)
/PA2_6: J4.15, U2.11 (PA6)
/PA2_7: J4.17, U2.12 (PA7)
/PB1_0: J1.4, U1.18 (PB0)
/PB1_1: J1.6, U1.19 (PB1)
/PB1_2: J1.8, U1.22 (PB2)
/PB1_3: J1.10, U1.23 (PB3)
/PB1_4: J1.12, U1.24 (PB4)
/PB1_5: J1.14, U1.25 (PB5)
/PB1_6: J1.16, U1.26 (PB6)
/PB1_7: J1.18, U1.27 (PB7)
/PB2_0: J4.4, U2.18 (PB0)
/PB2_1: J4.6, U2.19 (PB1)
/PB2_2: J4.8, U2.22 (PB2)
/PB2_3: J4.10, U2.23 (PB3)
/PB2_4: J4.12, U2.24 (PB4)
/PB2_5: J4.14, U2.25 (PB5)
/PB2_6: J4.16, U2.26 (PB6)
/PB2_7: J4.18, U2.27 (PB7)
/PC1_0: J5.3, U1.34 (PC0)
/PC1_1: J5.4, U1.35 (PC1)
/PC1_2: J5.5, U1.36 (TIN/PC2)
/PC1_3: J5.6, J8.1, J8.3, J8.5, J8.7, U1.37 (PC3/TOUT)
/PC1_4: J5.7, U1.38 (DMAREQ/PC4)
/PC1_5: J5.8, U1.39 (PC5/PIRQ)
/PC1_6: J5.9, U1.40 (PC6/PIACK)
/PC1_7: J5.10, J9.1, J9.3, J9.5, J9.7, R1.1, U1.41 (PC7/TIACK)
/PC2_0: J15.3, U2.34 (PC0)
/PC2_1: J15.4, U2.35 (PC1)
/PC2_2: J15.5, U2.36 (TIN/PC2)
/PC2_3: J10.1, J10.3, J10.5, J10.7, J15.6, U2.37 (PC3/TOUT)
/PC2_4: J15.7, U2.38 (DMAREQ/PC4)
/PC2_5: J15.8, U2.39 (PC5/PIRQ)
/PC2_6: J15.9, U2.40 (PC6/PIACK)
/PC2_7: J11.1, J11.3, J11.5, J11.7, J15.10, R2.1, U2.41 (PC7/TIACK)
/PITA_CLK: J2.2, U1.44 (CLK)
/PITB_CLK: J6.2, U2.44 (CLK)
/R/~W: J3.44 (R/~W), U1.47 (R/~W), U2.47 (R/~W)
/~DTACK: J3.62 (~BUSACK), U1.46 (~DTACK), U2.46 (~DTACK)
/~IACK2: J3.77 (~IACK2), J9.2, J11.2
/~IACK3: J3.78 (~IACK3), J9.4, J11.4
/~IACK5: J3.79 (~IACK5), J9.6, J11.6
/~IACK6: J3.80 (~IACK6), J9.8, J11.8
/~INT2: J3.37 (~INT2), J8.2, J10.2
/~INT3: J3.38 (~INT3), J8.4, J10.4
/~INT5: J3.39 (~INT5), J8.6, J10.6
/~INT6: J3.40 (~INT6), J8.8, J10.8
/~LDS: J3.43 (~LDS), U4.1 (G)
/~PITA_CS: J12.1, J12.2, J12.3, J12.4, J12.5, J12.6, J12.7, J12.8, U1.45 (~CS)
/~PITB_CS: J13.1, J13.2, J13.3, J13.4, J13.5, J13.6, J13.7, J13.8, U2.45 (~CS)
/~RESET: J3.20 (~RESET), U1.43 (~RESET), U2.43 (~RESET)
GND: C1.2, C2.2, C3.1, C4.1, J1.19, J1.20, J3.17 (GND), J3.57 (GND), J4.19, J4.20, J5.11, J5.12, J15.11, J15.12, U1.42 (GND), U2.42 (GND), U3.8 (GND), U4.5 (R1), U4.9 (R3), U4.10 (GND), U4.12 (R4), U4.14 (R5), U4.16 (R6)
unnamed: J7.1, U3.15 (O0)
unnamed: J7.2, U3.14 (O1)
unnamed: J7.3, U3.13 (O2)
unnamed: J7.4, U3.12 (O3)
unnamed: J7.5, U3.11 (O4)
unnamed: J7.6, U3.10 (O5)
unnamed: J7.7, U3.9 (O6)
unnamed: J7.8, U3.7 (O7)
unnamed: U3.4 (E1), U4.19 (P=R)

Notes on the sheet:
PI/T #2 TIMER INT ACK
PI/T #1 TIMER INT ACK
PI/T #2
CS0: D08000 CS1: D08800 CS2: D09000 CS3: D09800 CS4: D0A000 CS5: D0A800 CS6: D0B000 CS7: D0B800
PI/T #1 PORT C
PI/T #1 TIMER INT
PI/T #2 TIMER INT
PI/T #2 PORT A & B
PI/T #2 PORT C
PI/T #1
PI/T #1 PORT A & B
